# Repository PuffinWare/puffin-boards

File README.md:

# Puffin Boards
Eagle files for the various baord created for the Particle based tools an libraries.

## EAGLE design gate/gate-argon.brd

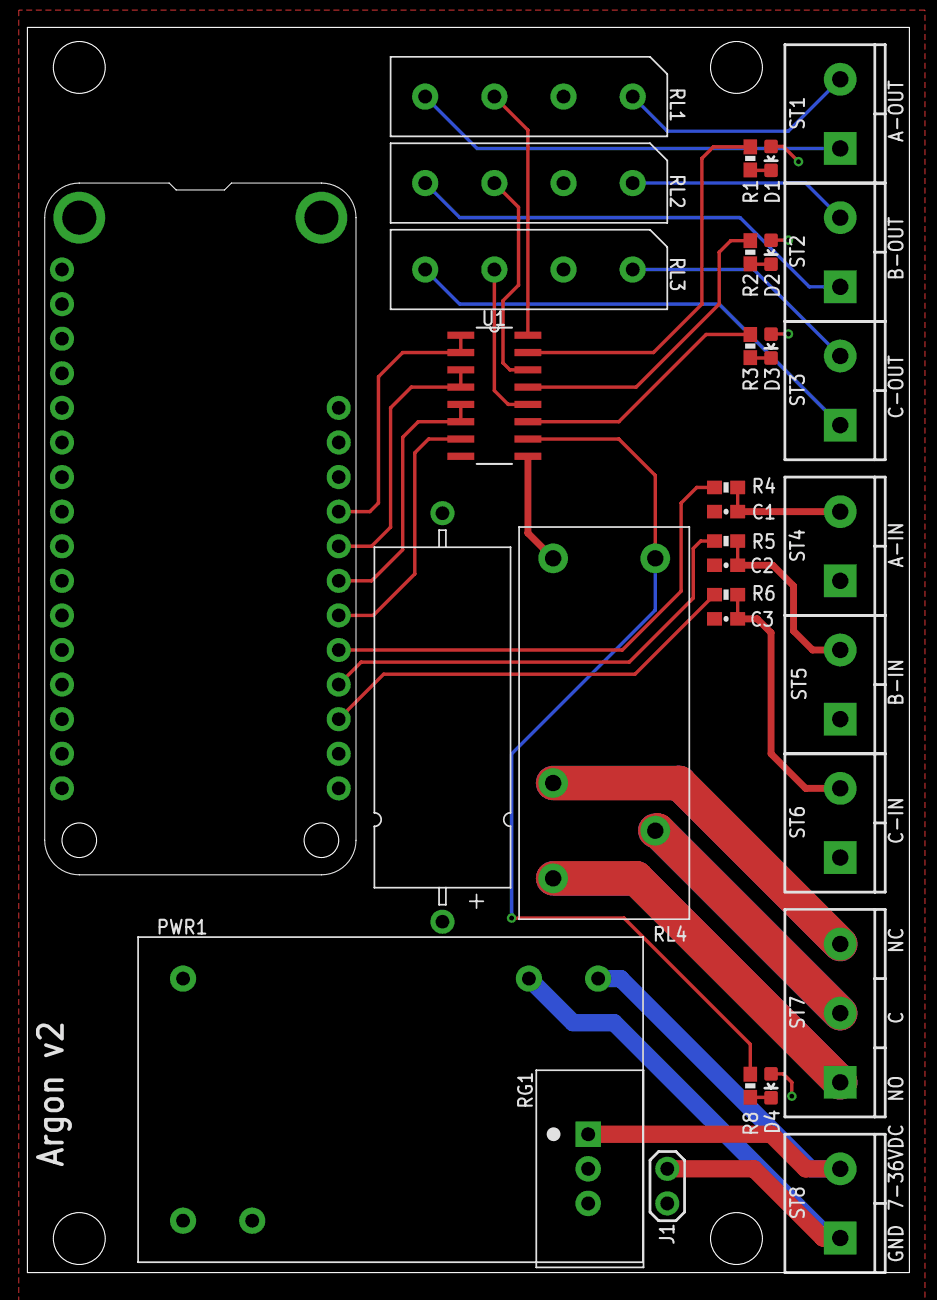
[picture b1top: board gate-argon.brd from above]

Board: 2 copper layers, 64.8 x 91.4 mm, 32 parts (0 on the bottom side), 34 nets.

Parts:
C1, C2, C3: .01u; 0603-CAP
C4: CAP-AXIAL-10X25
D1, D2, D3, D4: LED-0603
J1: 1X21X02-BIG; 1X02-BIG
MS2: FEATHERWING_NODIM; FEATHERWING_DIM
PWR1: IRM_03_PS_3W
R1, R2, R3, R8: 2.2K; 0603-RES
R4, R5, R6: 1K; 0603-RES
RG1: TRACO_TSR_2
RL1, RL2, RL3: HE3600_RELAY
RL4: G2RL_SPDT
ST1, ST2, ST3, ST4, ST5, ST6, ST8: SCREWTERM_0.2X2
ST7: SCREWTERM_0.2X3
U1: SN75468; SOIC16

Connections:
5V: C4.+, D1.A, D2.A, D3.A, D4.A, MS2.26, PWR1.V+, RG1.3, RL1.2, RL2.2, RL3.2, RL4.5, U1.9
GND: C1.2, C2.2, C3.2, C4.-, J1.1, MS2.4, PWR1.V-, RG1.2, ST4.1, ST5.1, ST6.1, U1.8
IN: PWR1.ACL, RG1.1, ST8.2
L5: RL3.3, U1.12
L6: R3.2, U1.11
L7: R8.2, RL4.1, U1.10
unnamed: D2.C, R2.1
unnamed: RL1.4, ST1.1
unnamed: D1.C, R1.1
unnamed: RL2.4, ST2.1
unnamed: R2.2, U1.13
unnamed: R1.2, U1.15
unnamed: C2.1, R5.1, ST5.2
unnamed: RL2.1, ST2.2
unnamed: RL3.1, ST3.2
unnamed: MS2.22, U1.7
unnamed: C3.1, R6.1, ST6.2
unnamed: RL1.1, ST1.2
unnamed: RL3.4, ST3.1
unnamed: D3.C, R3.1
unnamed: MS2.21, R4.2
unnamed: MS2.20, R5.2
unnamed: MS2.19, R6.2
unnamed: MS2.23, U1.5, U1.6
unnamed: J1.2, PWR1.ACN, ST8.1
unnamed: RL2.3, U1.14
unnamed: D4.C, R8.1
unnamed: MS2.25, U1.1, U1.2
unnamed: MS2.24, U1.3, U1.4
unnamed: C1.1, R4.1, ST4.2
unnamed: RL1.3, U1.16
RC: RL4.C, ST7.2
RNC: RL4.NC, ST7.3
RNO: RL4.NO, ST7.1

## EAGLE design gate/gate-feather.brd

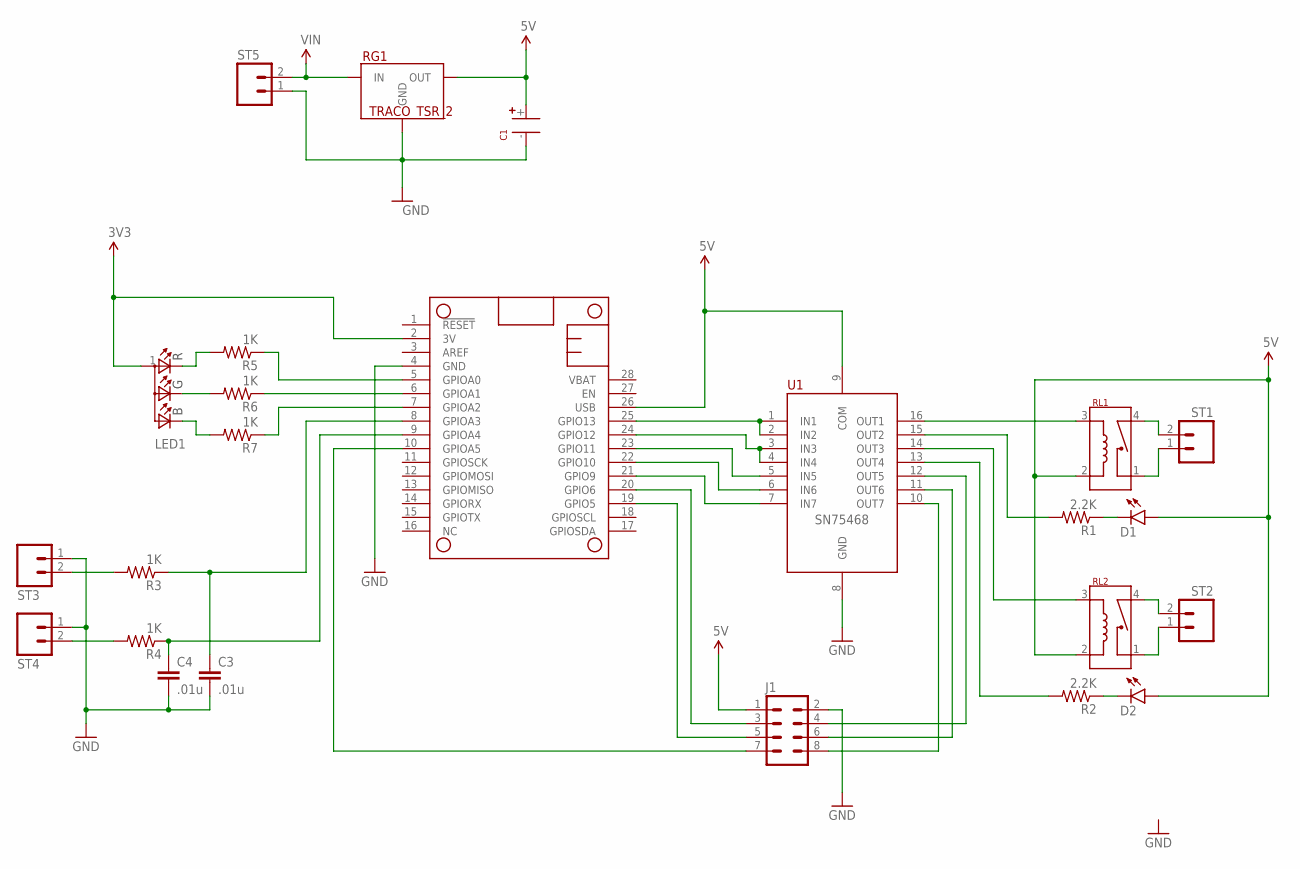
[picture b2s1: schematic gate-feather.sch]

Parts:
C1: CAPACITOR-AXIAL10X25; CAP-AXIAL-10X25
C3, C4: .01u; 0603-CAP
D1, D2: LED0603; LED-0603
J1: M04X2; 2X4
LED1: LED-RGB-CREE-SMD
MS1: FEATHERWING_NODIM; FEATHERWING_DIM
R1, R2: 2.2K; 0603-RES
R3, R4, R5, R6, R7: 1K; 0603-RES
RG1: TRACO_TSR_2
RL1, RL2: HE3600_RELAY
ST1, ST2, ST3, ST4, ST5: SCREWTERM_2; SCREWTERM_0.2X2
U1: SN75468; SOIC16

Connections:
3V3: LED1.1 (A), MS1.2 (3V)
5V: C1.+, D1.A, D2.A, J1.1, MS1.26 (USB), RG1.3 (OUT), RL1.2 (R1), RL2.2 (R1), U1.9 (COM)
GND: C1.-, C3.2, C4.2, J1.2, MS1.4 (GND), RG1.2 (GND), ST3.1, ST4.1, ST5.1, U1.8 (GND)
L5: J1.4, U1.12 (OUT5)
L6: J1.6, U1.11 (OUT6)
L7: J1.8, U1.10 (OUT7)
unnamed: D2.C, R2.1
unnamed: RL1.4 (C2), ST1.2
unnamed: D1.C, R1.1
unnamed: RL2.4 (C2), ST2.2
unnamed: R2.2, U1.13 (OUT4)
unnamed: R1.2, U1.15 (OUT2)
unnamed: C4.1, MS1.9 (GPIOA4), R4.1
unnamed: MS1.23 (GPIO11), U1.5 (IN5)
unnamed: RL2.1 (C1), ST2.1
unnamed: LED1.4 (R), R5.2
unnamed: LED1.3 (G), R6.2
unnamed: LED1.2 (B), R7.2
unnamed: RL1.1 (C1), ST1.1
unnamed: MS1.6 (GPIOA1), R6.1
unnamed: MS1.5 (GPIOA0), R5.1
unnamed: R4.2, ST4.2
unnamed: R3.2, ST3.2
unnamed: MS1.7 (GPIOA2), R7.1
unnamed: J1.3, MS1.20 (GPIO6)
unnamed: MS1.22 (GPIO10), U1.6 (IN6)
unnamed: RL2.3 (R2), U1.14 (OUT3)
unnamed: MS1.21 (GPIO9), U1.7 (IN7)
unnamed: J1.5, MS1.19 (GPIO5)
unnamed: J1.7, MS1.10 (GPIOA5)
unnamed: MS1.25 (GPIO13), U1.1 (IN1), U1.2 (IN2)
unnamed: MS1.24 (GPIO12), U1.3 (IN3), U1.4 (IN4)
unnamed: C3.1, MS1.8 (GPIOA3), R3.1
unnamed: RL1.3 (R2), U1.16 (OUT1)
VIN: RG1.1 (IN), ST5.2

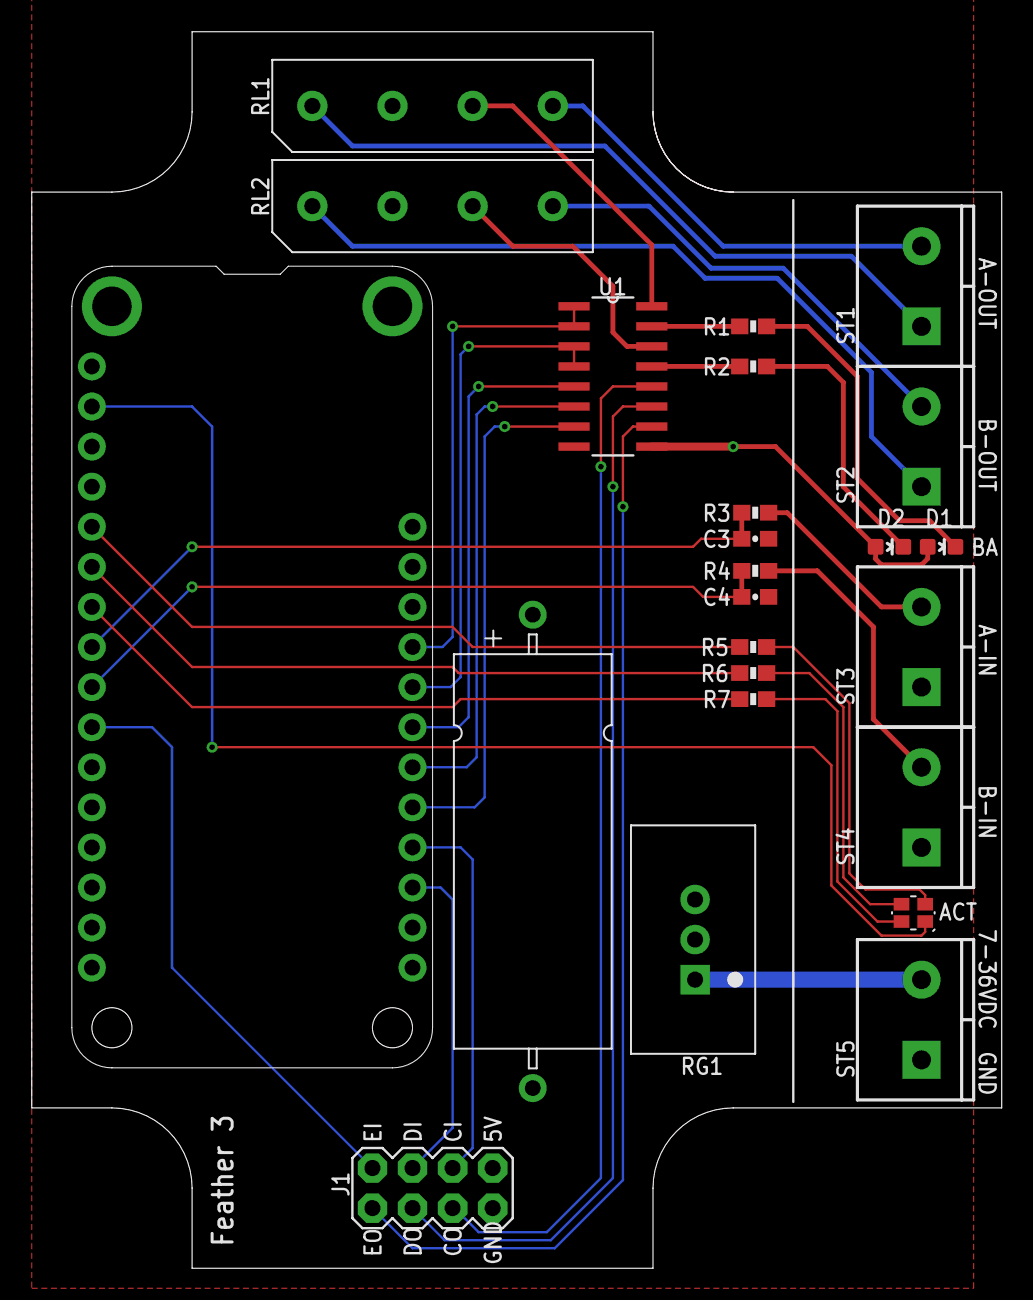
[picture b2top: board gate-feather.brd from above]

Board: 2 copper layers, 61.5 x 78.4 mm, 24 parts (0 on the bottom side), 35 nets.

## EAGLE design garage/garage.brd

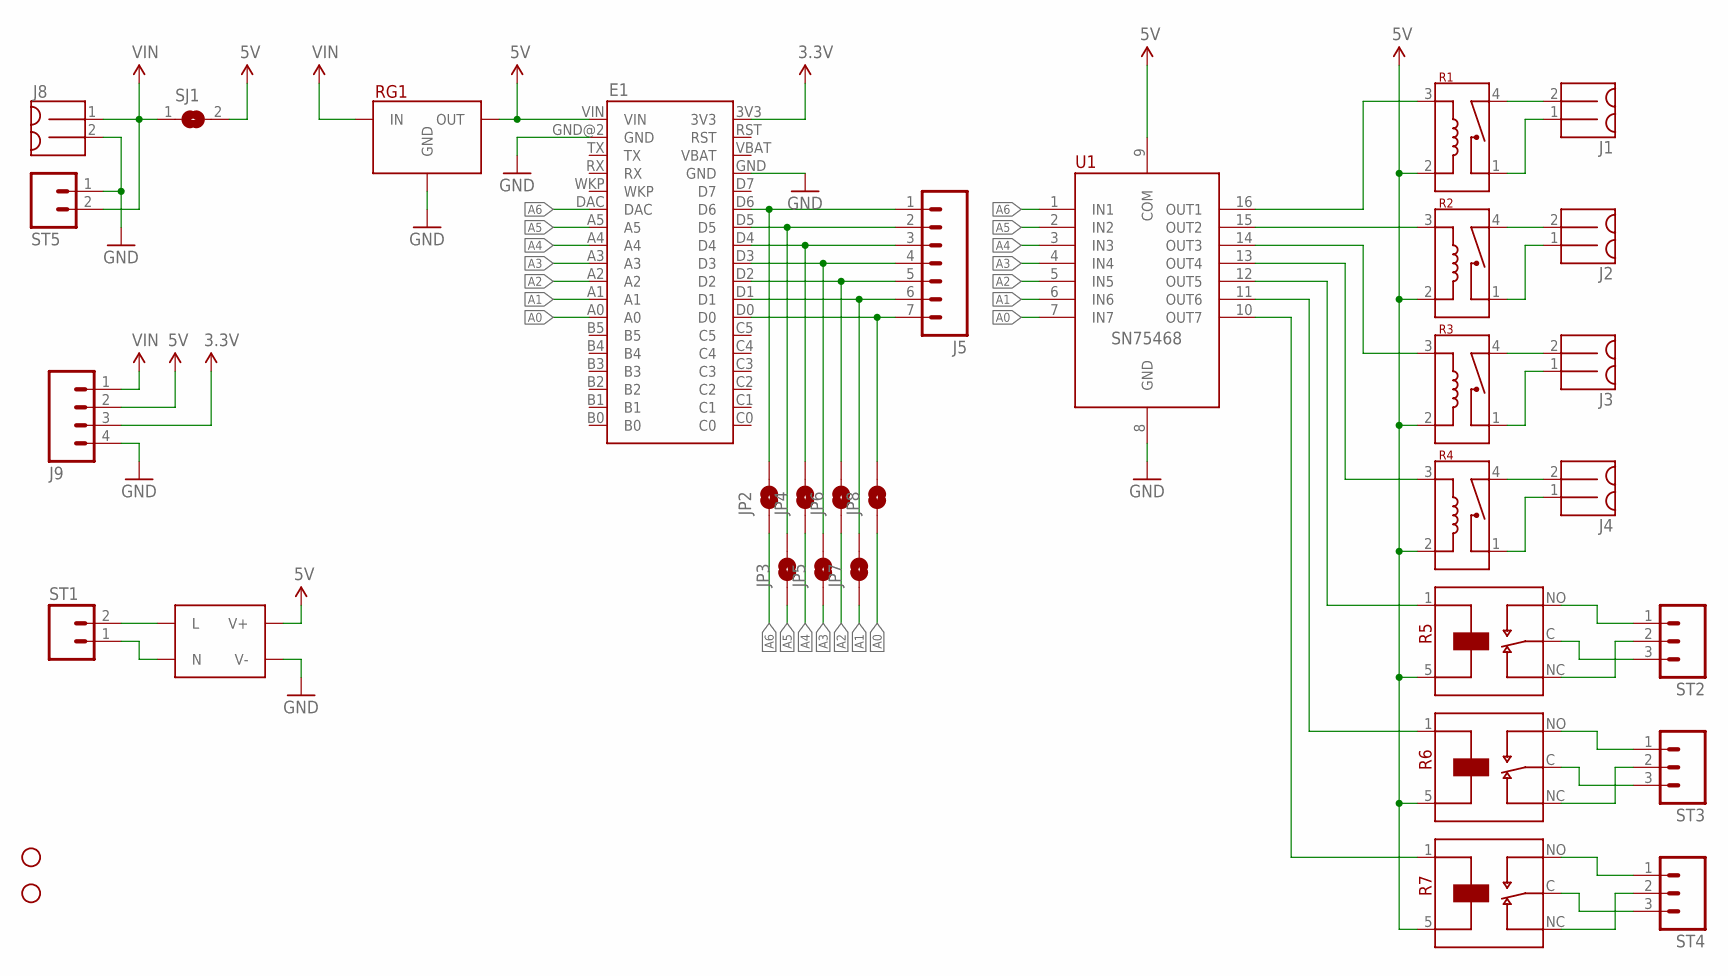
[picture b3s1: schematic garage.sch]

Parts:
E1: ELECTRON
H1, H2: STAND-OFF
J1, J2, J3, J4, J8: MOLEX_MINILITE_TRAP_2
J5: M07; 1X07
J9: M04PTH; 1X04
JP2, JP3, JP4, JP5, JP6, JP7, JP8: JUMPER-PAD-2-NOYES_SILK; PAD-JUMPER-2-NO_YES_SILK
PS1: IRM_03_PS_3W
R1, R2, R3, R4: HE3600_RELAY
R5, R6, R7: G2RL_SPDT
RG1: MURATA_REG; MURATA_REG_HOR
SJ1: SJ
ST1, ST5: SCREWTERM_2; SCREWTERM_0.2X2
ST2, ST3, ST4: SCREWTERM_3; SCREWTERM_0.2X3
U1: SN75468; SOIC16

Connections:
3.3V: E1.3V3, J9.3
5V: E1.VIN, J9.2, PS1.V+, R1.2 (R1), R2.2 (R1), R3.2 (R1), R4.2 (R1), R5.5, R6.5, R7.5, RG1.3 (OUT), SJ1.2, U1.9 (COM)
A0: E1.A0, JP8.1, U1.7 (IN7)
A1: E1.A1, JP7.1, U1.6 (IN6)
A2: E1.A2, JP6.1, U1.5 (IN5)
A3: E1.A3, JP5.1, U1.4 (IN4)
A4: E1.A4, JP4.1, U1.3 (IN3)
A5: E1.A5, JP3.1, U1.2 (IN2)
A6: E1.DAC, JP2.1, U1.1 (IN1)
GND: E1.GND, E1.GND@2 (GND), J8.2, J9.4, PS1.V-, RG1.2 (GND), ST5.1, U1.8 (GND)
unnamed: PS1.ACL (L), ST1.2
unnamed: R4.3 (R2), U1.13 (OUT4)
unnamed: R5.1, U1.12 (OUT5)
unnamed: R6.1, U1.11 (OUT6)
unnamed: R7.1, U1.10 (OUT7)
unnamed: J4.2, R4.4 (C2)
unnamed: J3.2, R3.4 (C2)
unnamed: J2.2, R2.4 (C2)
unnamed: J2.1, R2.1 (C1)
unnamed: J3.1, R3.1 (C1)
unnamed: J4.1, R4.1 (C1)
unnamed: J1.2, R1.4 (C2)
unnamed: J1.1, R1.1 (C1)
unnamed: R6.NO, ST3.1
unnamed: R6.NC, ST3.2
unnamed: R5.NO, ST2.1
unnamed: R5.C, ST2.3
unnamed: R6.C, ST3.3
unnamed: R7.NC, ST4.2
unnamed: R7.C, ST4.3
unnamed: R5.NC, ST2.2
unnamed: R2.3 (R2), U1.15 (OUT2)
unnamed: PS1.ACN (N), ST1.1
unnamed: R7.NO, ST4.1
unnamed: E1.D0, J5.7, JP8.2
unnamed: E1.D1, J5.6, JP7.2
unnamed: E1.D2, J5.5, JP6.2
unnamed: R1.3 (R2), U1.16 (OUT1)
unnamed: E1.D3, J5.4, JP5.2
unnamed: R3.3 (R2), U1.14 (OUT3)
unnamed: E1.D4, J5.3, JP4.2
unnamed: E1.D5, J5.2, JP3.2
unnamed: E1.D6, J5.1, JP2.2
VIN: J8.1, J9.1, RG1.1 (IN), SJ1.1, ST5.2

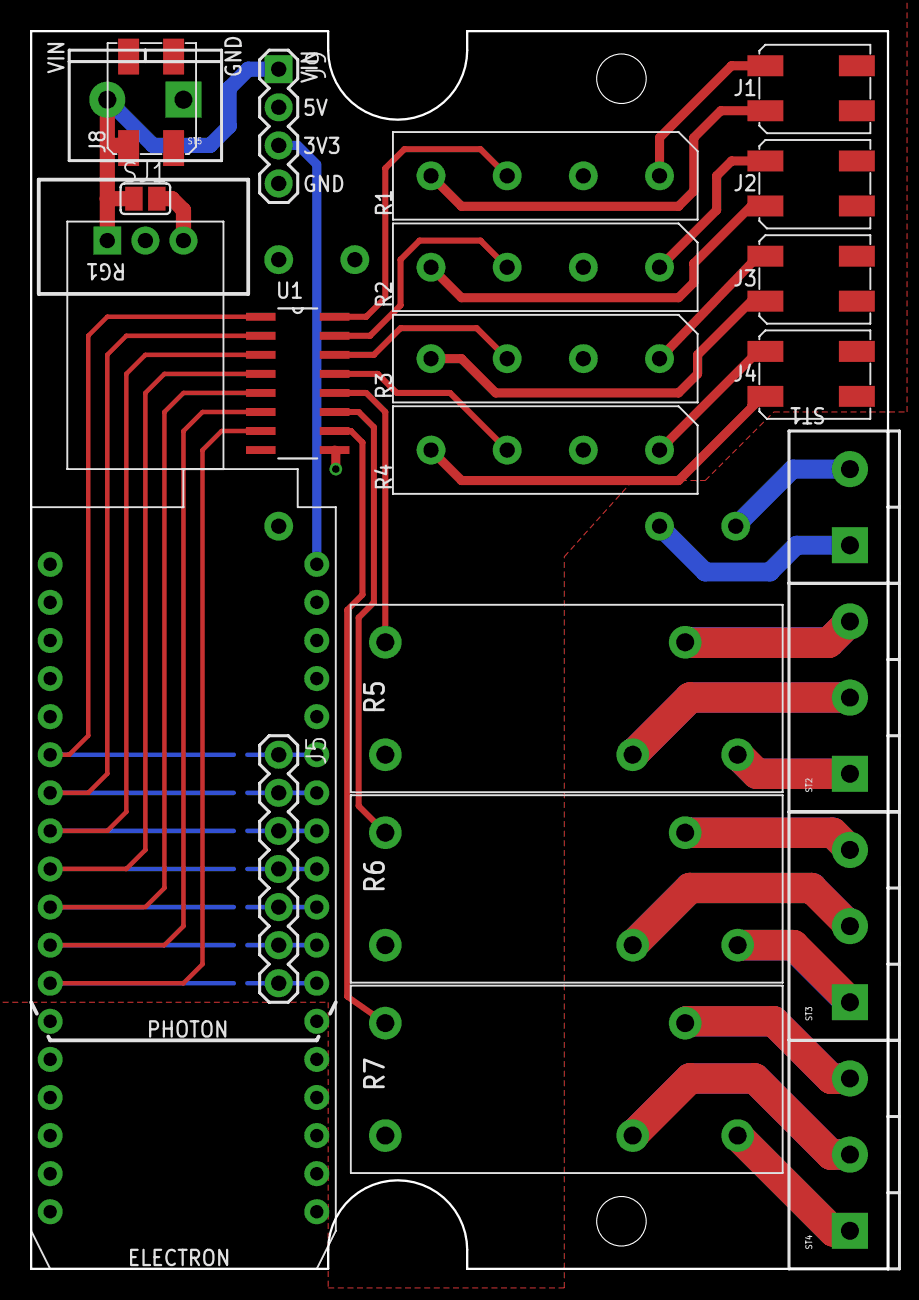
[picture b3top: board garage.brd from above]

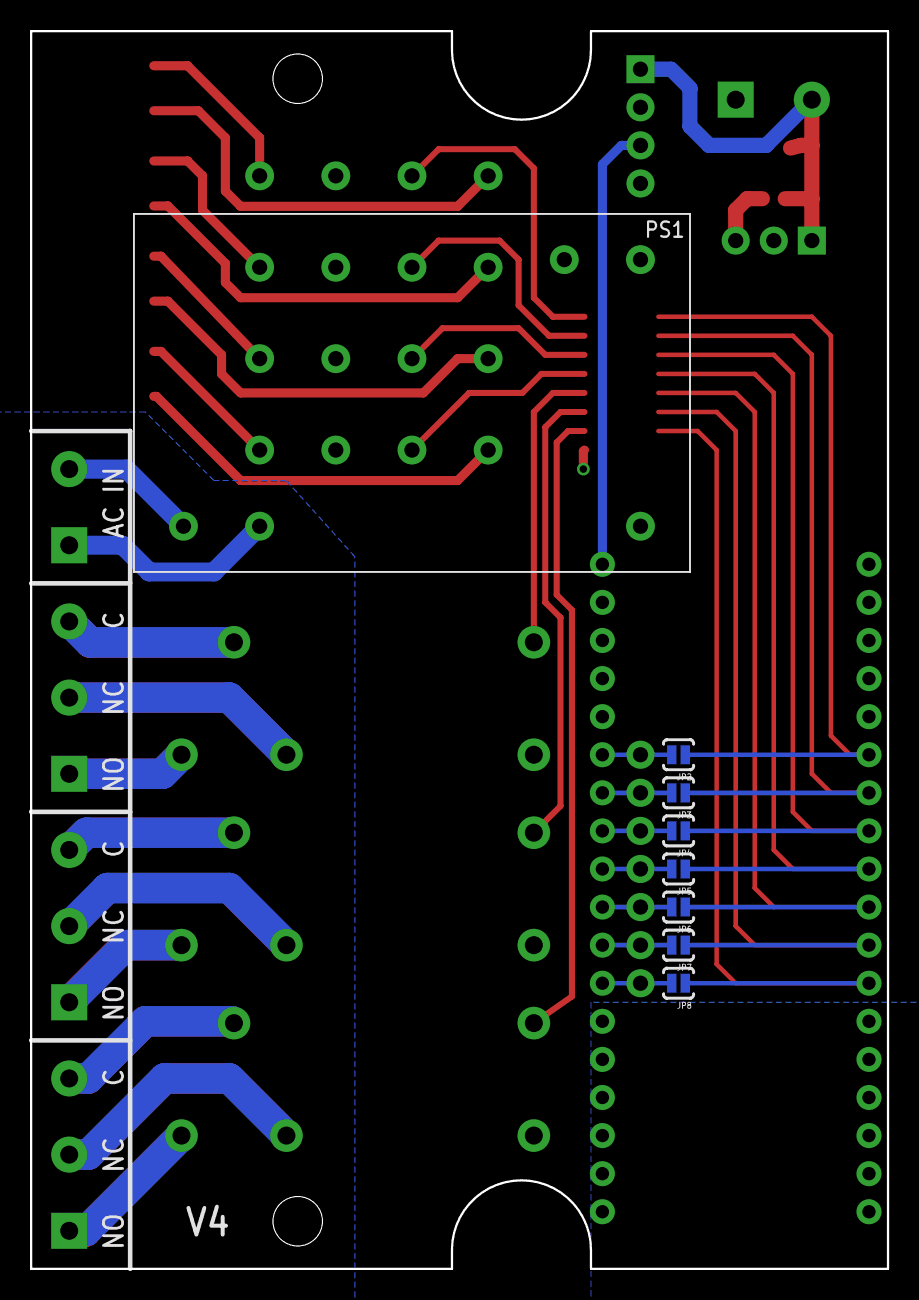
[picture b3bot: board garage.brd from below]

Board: 2 copper layers, 57.1 x 82.5 mm, 33 parts (8 on the bottom side), 44 nets.

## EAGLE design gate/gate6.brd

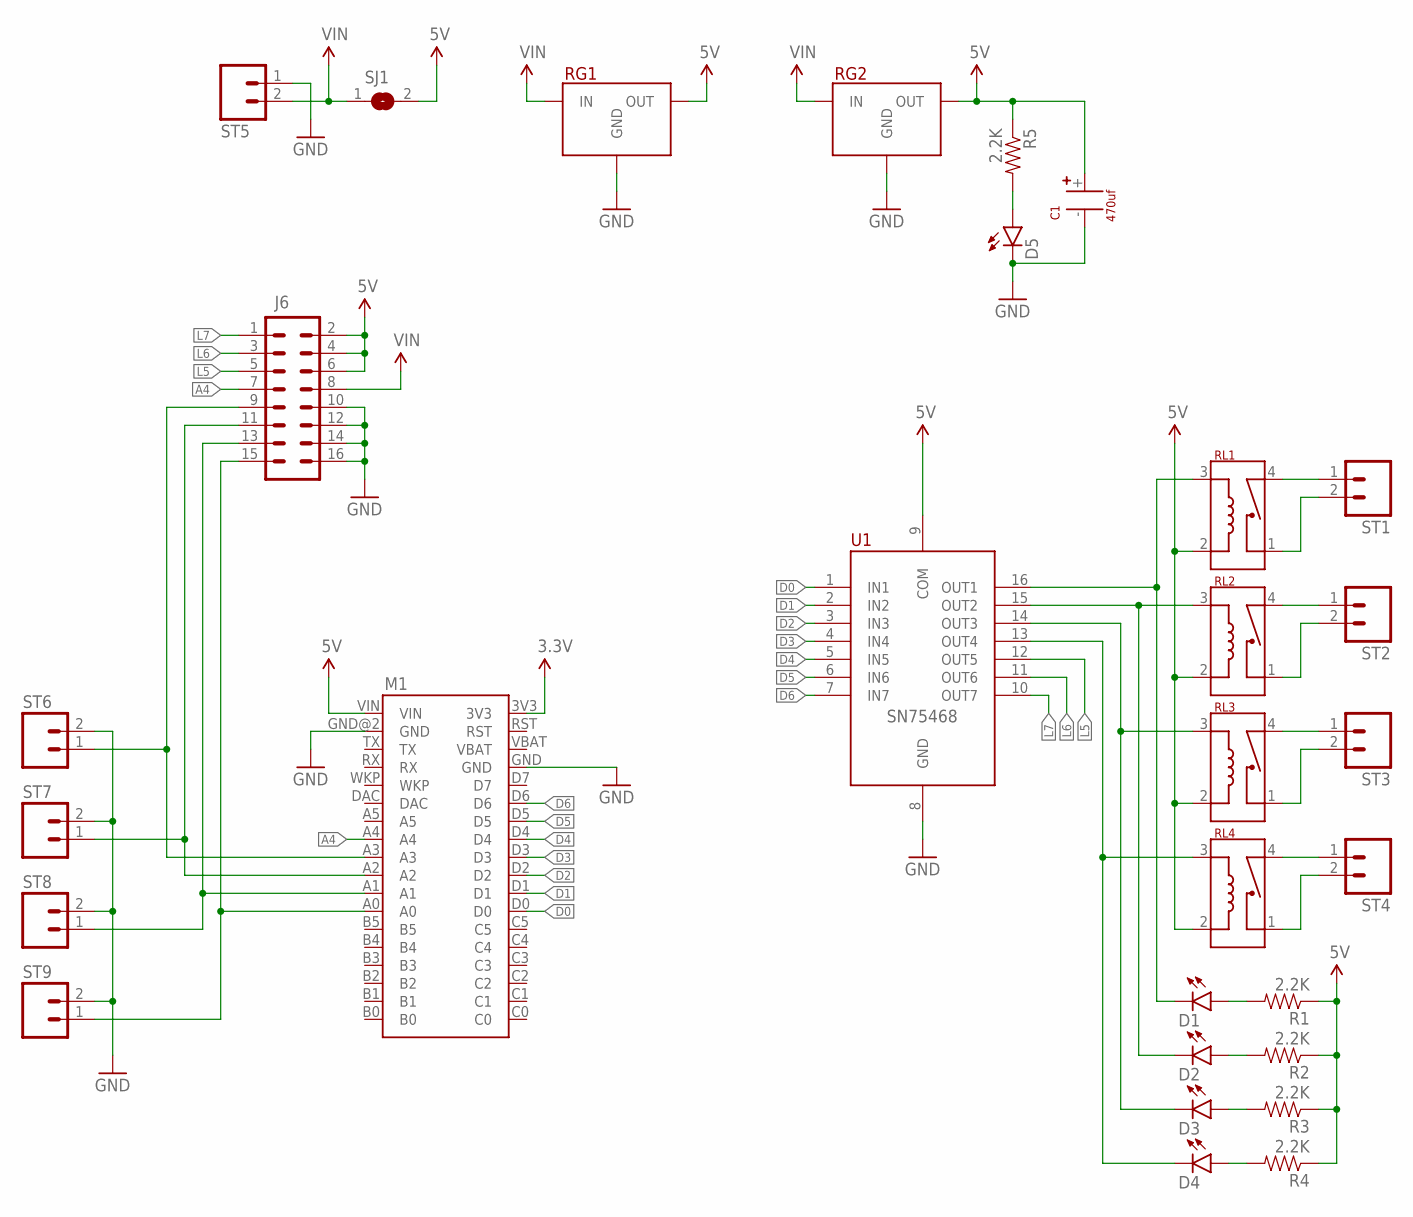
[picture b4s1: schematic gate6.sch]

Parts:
C1: 470uf; CAP-AXIAL-10X25
D1, D2, D3, D4, D5: LED0603; LED-0603
J6: M08X2; 2X8
M1: ELECTRON
R1, R2, R3, R4, R5: 2.2K; 0603-RES
RG1: MURATA_REG; MURATA_REG_HOR
RG2: TRACO_TSR_2
RL1, RL2, RL3, RL4: HE3600_RELAY
SJ1: SJ
ST1, ST2, ST3, ST4, ST5, ST6, ST7, ST8, ST9: SCREWTERM_2; SCREWTERM_0.2X2
U1: SN75468; SOIC16

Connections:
3.3V: M1.3V3
5V: C1.+, J6.2, J6.4, J6.6, M1.VIN, R1.1, R2.1, R3.1, R4.1, R5.1, RG1.3 (OUT), RG2.3 (OUT), RL1.2 (R1), RL2.2 (R1), RL3.2 (R1), RL4.2 (R1), SJ1.2, U1.9 (COM)
A4: J6.7, M1.A4
D0: M1.D0, U1.1 (IN1)
D1: M1.D1, U1.2 (IN2)
D2: M1.D2, U1.3 (IN3)
D3: M1.D3, U1.4 (IN4)
D4: M1.D4, U1.5 (IN5)
D5: M1.D5, U1.6 (IN6)
D6: M1.D6, U1.7 (IN7)
GND: C1.-, D5.C, J6.10, J6.12, J6.14, J6.16, M1.GND, M1.GND@2 (GND), RG1.2 (GND), RG2.2 (GND), ST5.1, ST6.2, ST7.2, ST8.2, ST9.2, U1.8 (GND)
L5: J6.5, U1.12 (OUT5)
L6: J6.3, U1.11 (OUT6)
L7: J6.1, U1.10 (OUT7)
unnamed: D2.A, R2.2
unnamed: D4.C, RL4.3 (R2), U1.13 (OUT4)
unnamed: D1.A, R1.2
unnamed: D3.A, R3.2
unnamed: D4.A, R4.2
unnamed: RL4.4 (C2), ST4.1
unnamed: RL3.4 (C2), ST3.1
unnamed: RL2.4 (C2), ST2.1
unnamed: RL2.1 (C1), ST2.2
unnamed: RL3.1 (C1), ST3.2
unnamed: RL4.1 (C1), ST4.2
unnamed: RL1.4 (C2), ST1.1
unnamed: RL1.1 (C1), ST1.2
unnamed: D5.A, R5.2
unnamed: J6.15, M1.A0, ST9.1
unnamed: J6.13, M1.A1, ST8.1
unnamed: J6.11, M1.A2, ST7.1
unnamed: J6.9, M1.A3, ST6.1
unnamed: D2.C, RL2.3 (R2), U1.15 (OUT2)
unnamed: D1.C, RL1.3 (R2), U1.16 (OUT1)
unnamed: D3.C, RL3.3 (R2), U1.14 (OUT3)
VIN: J6.8, RG1.1 (IN), RG2.1 (IN), SJ1.1, ST5.2

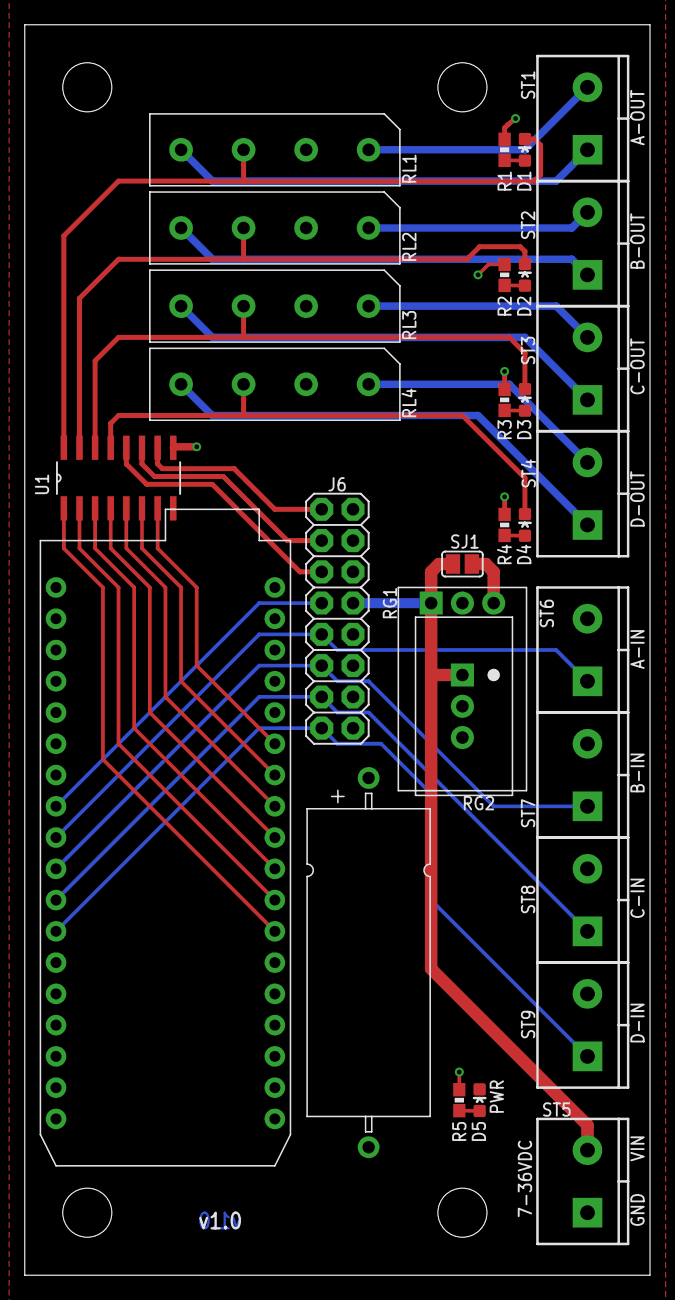
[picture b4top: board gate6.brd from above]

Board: 2 copper layers, 50.8 x 101.6 mm, 30 parts (0 on the bottom side), 35 nets.

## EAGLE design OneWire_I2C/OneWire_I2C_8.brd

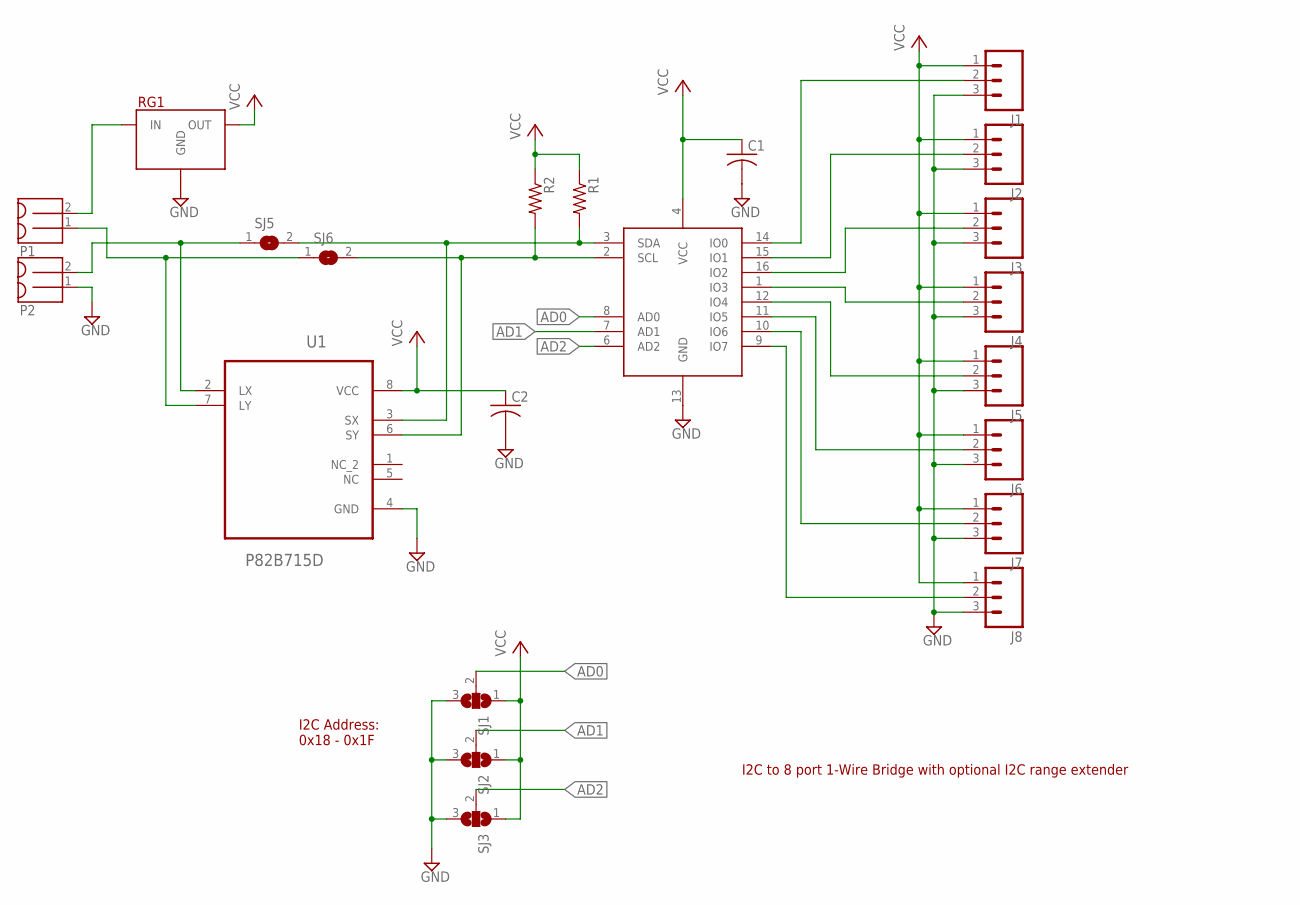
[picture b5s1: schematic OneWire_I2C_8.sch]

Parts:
C1, C2: C-USC0603; C0603
J1, J2, J3, J4, J5, J6, J7, J8: M03PTH; 1X03
P1, P2: MOLEX_MINILITE_TRAP_2
R1, R2: RESISTOR0603-RES; 0603-RES
RG1: MURATA_REG; MURATA_REG_HOR
SJ1, SJ2, SJ3: SJ2W; SJ_2
SJ5, SJ6: SJ
U1: P82B715D; SOIC127P600X175-8N
W1: DS2482-800; SOIC16

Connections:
AD0: SJ1.2, W1.8 (AD0)
AD1: SJ2.2, W1.7 (AD1)
AD2: SJ3.2, W1.6 (AD2)
GND: C1.2, C2.2, J1.3, J2.3, J3.3, J4.3, J5.3, J6.3, J7.3, J8.3, P2.1, RG1.2 (GND), SJ1.3, SJ2.3, SJ3.3, U1.4 (GND), W1.13 (GND)
IN: P1.2, RG1.1 (IN)
IO0: J1.2, W1.14 (IO0)
IO1: J2.2, W1.15 (IO1)
IO2: J3.2, W1.16 (IO2)
IO3: J4.2, W1.1 (IO3)
IO4: J5.2, W1.12 (IO4)
IO5: J6.2, W1.11 (IO5)
IO6: J7.2, W1.10 (IO6)
IO7: J8.2, W1.9 (IO7)
LY: P1.1, SJ6.1, U1.7 (LY)
unnamed: P2.2, SJ5.1, U1.2 (LX)
SCL: R2.2, SJ6.2, U1.6 (SY), W1.2 (SCL)
SDA: R1.2, SJ5.2, U1.3 (SX), W1.3 (SDA)
VCC: C1.1, C2.1, J1.1, J2.1, J3.1, J4.1, J5.1, J6.1, J7.1, J8.1, R1.1, R2.1, RG1.3 (OUT), SJ1.1, SJ2.1, SJ3.1, U1.8 (VCC), W1.4 (VCC)

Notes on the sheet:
I2C Address: 0x18 - 0x1F
I2C to 8 port 1-Wire Bridge with optional I2C range extender

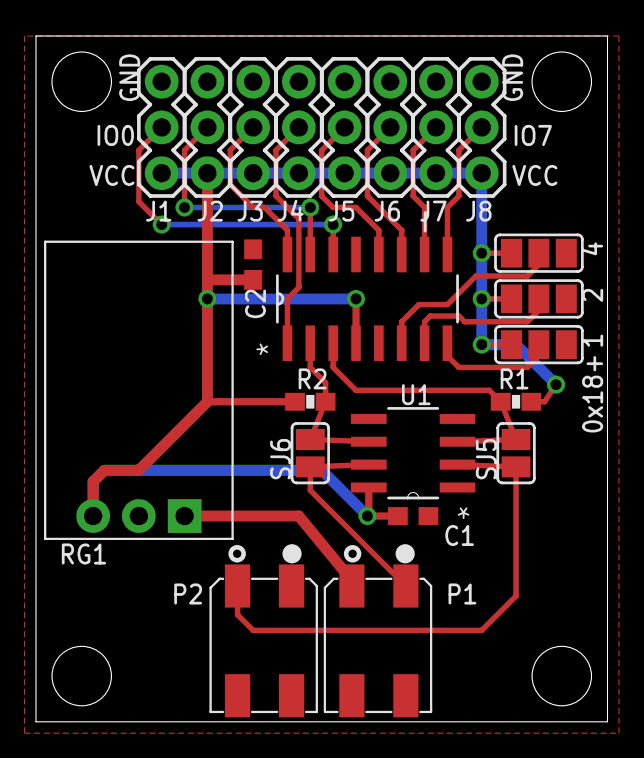
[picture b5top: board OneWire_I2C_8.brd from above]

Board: 2 copper layers, 31.8 x 38.1 mm, 26 parts (0 on the bottom side), 18 nets.

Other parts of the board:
U$1, U$2, U$3, U$4: STAND-OFF

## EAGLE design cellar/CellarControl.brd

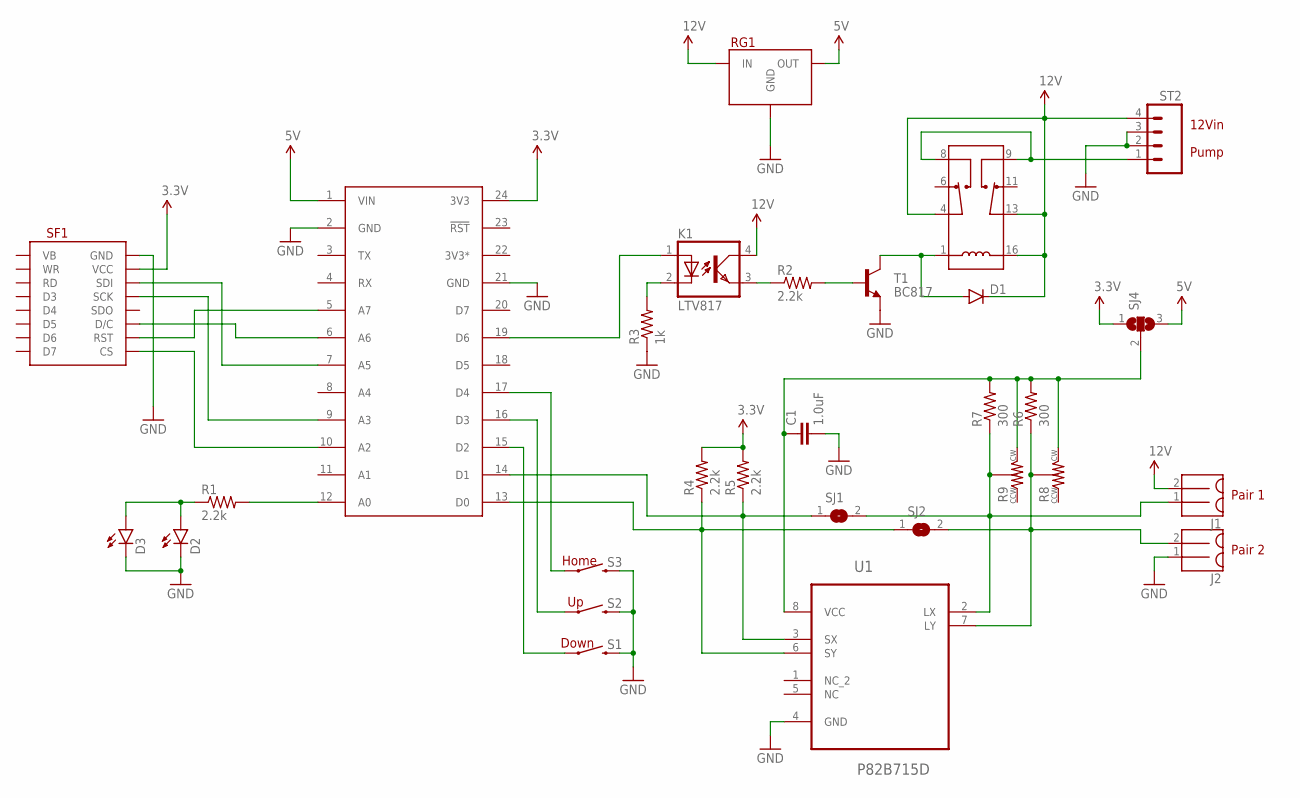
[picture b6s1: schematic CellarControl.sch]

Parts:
C1: 1.0uF; 0603-CAP
D1: DIODEKIT; DIODE-1N4148-KIT
D2: LED3MM
D3: LED0603; LED-0603
J1, J2: MOLEX_MINILITE_TRAP_2
K1: LTV817; DIP4
R1, R2, R4, R5: 2.2k; 0805
R3: 1k; 0805
R6, R7: 300; 0805
R8, R9: POT_3MM
RG1: MURATA_REG; MURATA_REG_HOR
RLY1: HK19F_5V_DPDT_RELAY; DIP16-RELAY
S1, S2, S3: SWITCH_MOMENT; SWITCH_MOMENT_6MM
SC1: SPARK_CORECORE; SPARK_CORE
SF1: SPARKFUN_OLED
SJ1, SJ2: SJ
SJ4: SJ2W; SJ_2
ST2: SCREWTERM_4; SCREWTERM_0.2X4
T1: BC817; SOT-23
U1: P82B715D; SOIC127P600X175-8N

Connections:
3.3V: R4.2, R5.2, SC1.24 (3V3), SF1.VDD (VCC), SJ4.1
3V3*: SC1.22 (3V3*)
5V: RG1.3 (OUT), SC1.1 (VIN), SJ4.3
12V: D1.C, J1.2, K1.4 (COL), RG1.1 (IN), RLY1.4 (C1), RLY1.13 (C2), RLY1.16 (L2), ST2.4
GND: C1.2, D2.K (C), D3.C, J2.1, R3.1, RG1.2 (GND), S1.3 (2), S1.4 (2), S2.3 (2), S2.4 (2), S3.3 (2), S3.4 (2), SC1.2 (GND), SC1.21 (GND), SF1.GND, ST2.2, ST2.3, T1.2 (E), U1.4 (GND)
LCL: J1.1, R7.1, R9.2, SJ1.2, U1.2 (LX)
LDA: J2.2, R6.1, R8.2, SJ2.2, U1.7 (LY)
unnamed: RLY1.8 (NO1), RLY1.9 (NO2), ST2.1
unnamed: D2.A, D3.A, R1.1
unnamed: R1.2, SC1.12 (A0)
unnamed: SC1.7 (A5), SF1.SDI
unnamed: SC1.9 (A3), SF1.SCK
unnamed: SC1.10 (A2), SF1.CS
unnamed: SC1.6 (A6), SF1.D/C
unnamed: SC1.5 (A7), SF1.RST
unnamed: S1.1, S1.2 (1), SC1.15 (D2)
unnamed: S2.1, S2.2 (1), SC1.16 (D3)
unnamed: S3.1, S3.2 (1), SC1.17 (D4)
unnamed: D1.A, RLY1.1 (L1), T1.3 (C)
unnamed: K1.2 (C), R3.2
unnamed: K1.1 (A), SC1.19 (D6)
unnamed: K1.3 (EMIT), R2.1
unnamed: R2.2, T1.1 (B)
SCL: R5.1, SC1.14 (D1), SJ1.1, U1.3 (SX)
SDA: R4.1, SC1.13 (D0), SJ2.1, U1.6 (SY)
VSEL: C1.1, R6.2, R7.2, R8.3, R9.3, SJ4.2, U1.8 (VCC)

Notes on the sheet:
12Vin
Pump
Pair 1
Pair 2
Home
Down

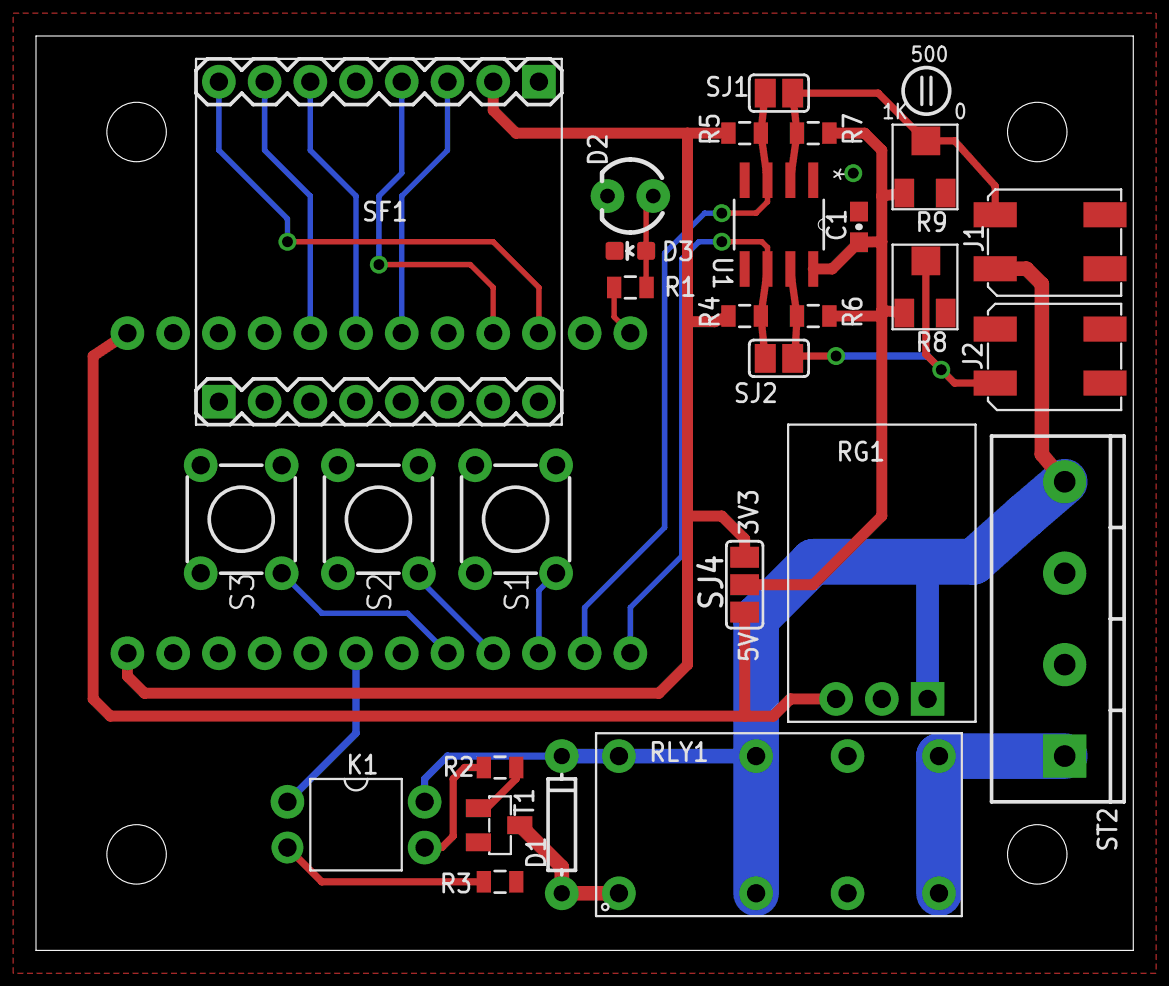
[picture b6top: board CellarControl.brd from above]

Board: 2 copper layers, 61.0 x 50.8 mm, 33 parts (1 on the bottom side), 25 nets.

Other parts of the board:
U$2, U$4, U$5, U$6: STAND-OFF

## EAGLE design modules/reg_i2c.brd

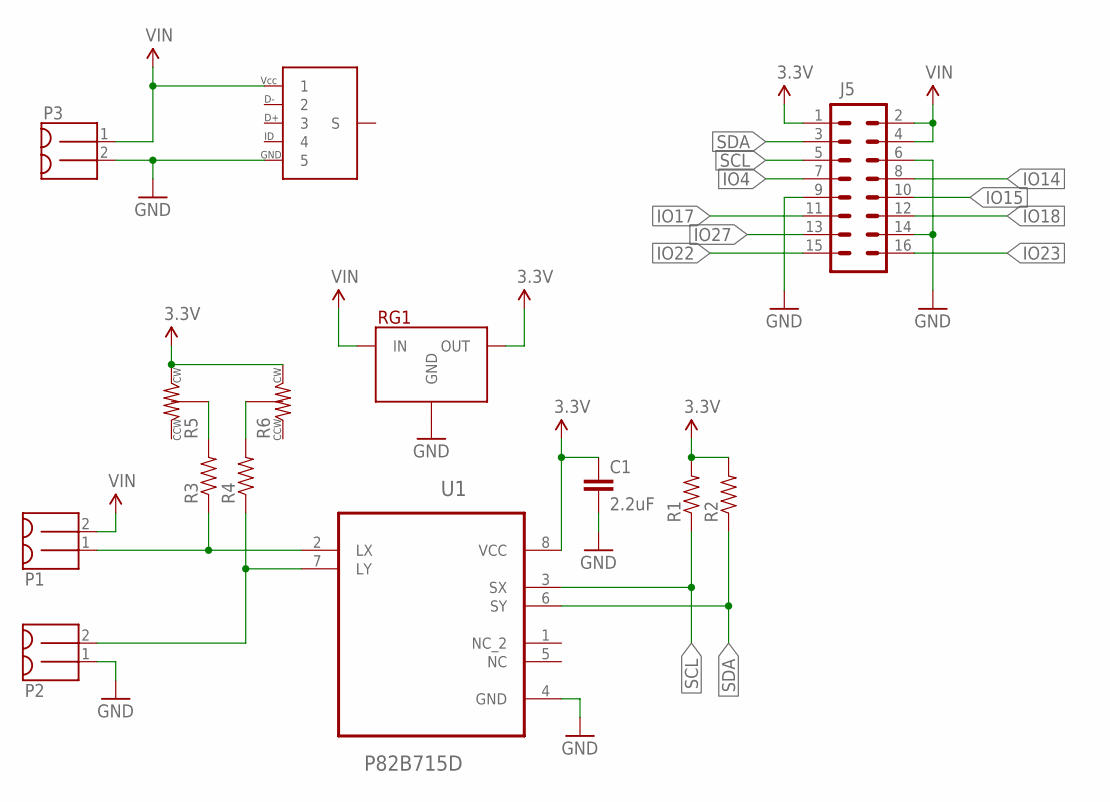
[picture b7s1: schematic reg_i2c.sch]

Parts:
C1: 2.2uF; 0603-CAP
J5: M08X2; 2X8
P1, P2, P3: MOLEX_MINILITE_TRAP_2
R1, R2, R3, R4: RESISTOR0805-RES; 0805
R5, R6: POT_3MM
RG1: MURATA_REG; MURATA_REG_HOR
U1: P82B715D; SOIC127P600X175-8N
U$1: USB_MICRO; USB_MICROB_MOLEX

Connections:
3.3V: C1.1, J5.1, R1.2, R2.2, R5.3, R6.3, RG1.3 (OUT), U1.8 (VCC)
GND: C1.2, J5.6, J5.9, J5.14, P2.1, P3.2, RG1.2 (GND), U1.4 (GND), U$1.5
IO4: J5.7
IO14: J5.8
IO15: J5.10
IO17: J5.11
IO18: J5.12
IO22: J5.15
IO23: J5.16
IO27: J5.13
unnamed: R4.2, R6.2
unnamed: R3.2, R5.2
unnamed: P2.2, R4.1, U1.7 (LY)
unnamed: P1.1, R3.1, U1.2 (LX)
SCL: J5.5, R1.1, U1.3 (SX)
SDA: J5.3, R2.1, U1.6 (SY)
VIN: J5.2, J5.4, P1.2, P3.1, RG1.1 (IN), U$1.1

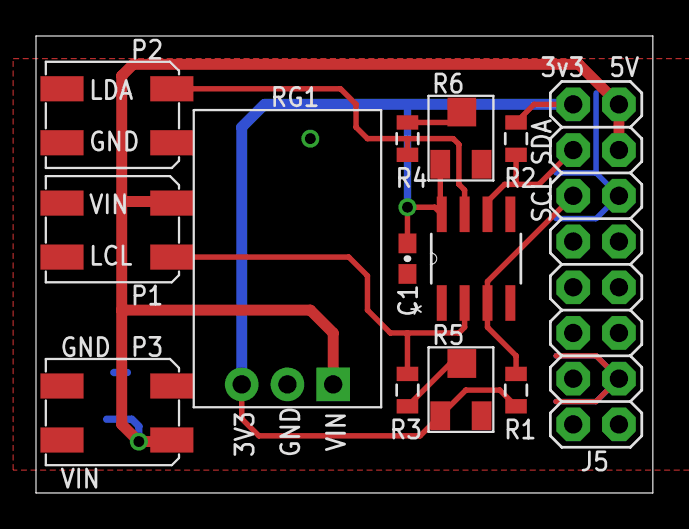
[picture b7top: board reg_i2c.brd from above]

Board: 2 copper layers, 34.3 x 25.4 mm, 14 parts (1 on the bottom side), 9 nets.

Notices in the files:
parts and their libraries:
SparkFun-Connectors: Licensing: Creative Commons ShareAlike 4.0 International - https://creativecommons.org/licenses/by-sa/4.0
